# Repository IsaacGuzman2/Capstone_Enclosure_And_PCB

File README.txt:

Hi future student!

IF you are reading this congrats you get to continue a cool project that I had the pleasure of getting to start for my capstone.

This folder contains the enclosures and PCB files that I made for this project. I was mainly in charge of the more physical aspects of this project so any questions about that you can contact me about through my school email (guzmange@oregonstate.edu) 

I'd be more then happy to help with any questions. This stuff is free use so don't be afraid to delete, add, or modify in any way you see fit. I understand you will have to make your own engineering requirements so go off I guess. 

I wish you the best in this project don't forget to communicate with Gerrad he has some good ideas and even is really motivating. This project has some real impact so be proud of what you accomplish and relly try your best and you will be rewarded by making a positive impact in the world. 

Godspeed homies

Gerardo Isaac Guzman

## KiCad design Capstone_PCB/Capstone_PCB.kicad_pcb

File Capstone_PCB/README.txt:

Hi again future student!

This here is the Kicad Project files for the Main PCB 

This PCB has the schematic and pcb files for the project as well as a folder for the gerber files to get our final version of the PCB printed by OSHPark

There should also be a .csv file here with the BOM that should help find which parts are needed in case something happens with carrying over the files. 

I HIGHLY reccomend ordering at another PCB print shop other then OSHPark because of the cost. It is a 2-layer board but it costs about $45+ with no rushed shipping (12-15 days) so it can get expensive. Please look at other options when ordering if money is an issue. 

Hopefully this file helps as always fell free to make adjustments to meet the capstone class requirements. 

Godspeed homies,

Gerardo Isaac Guzman

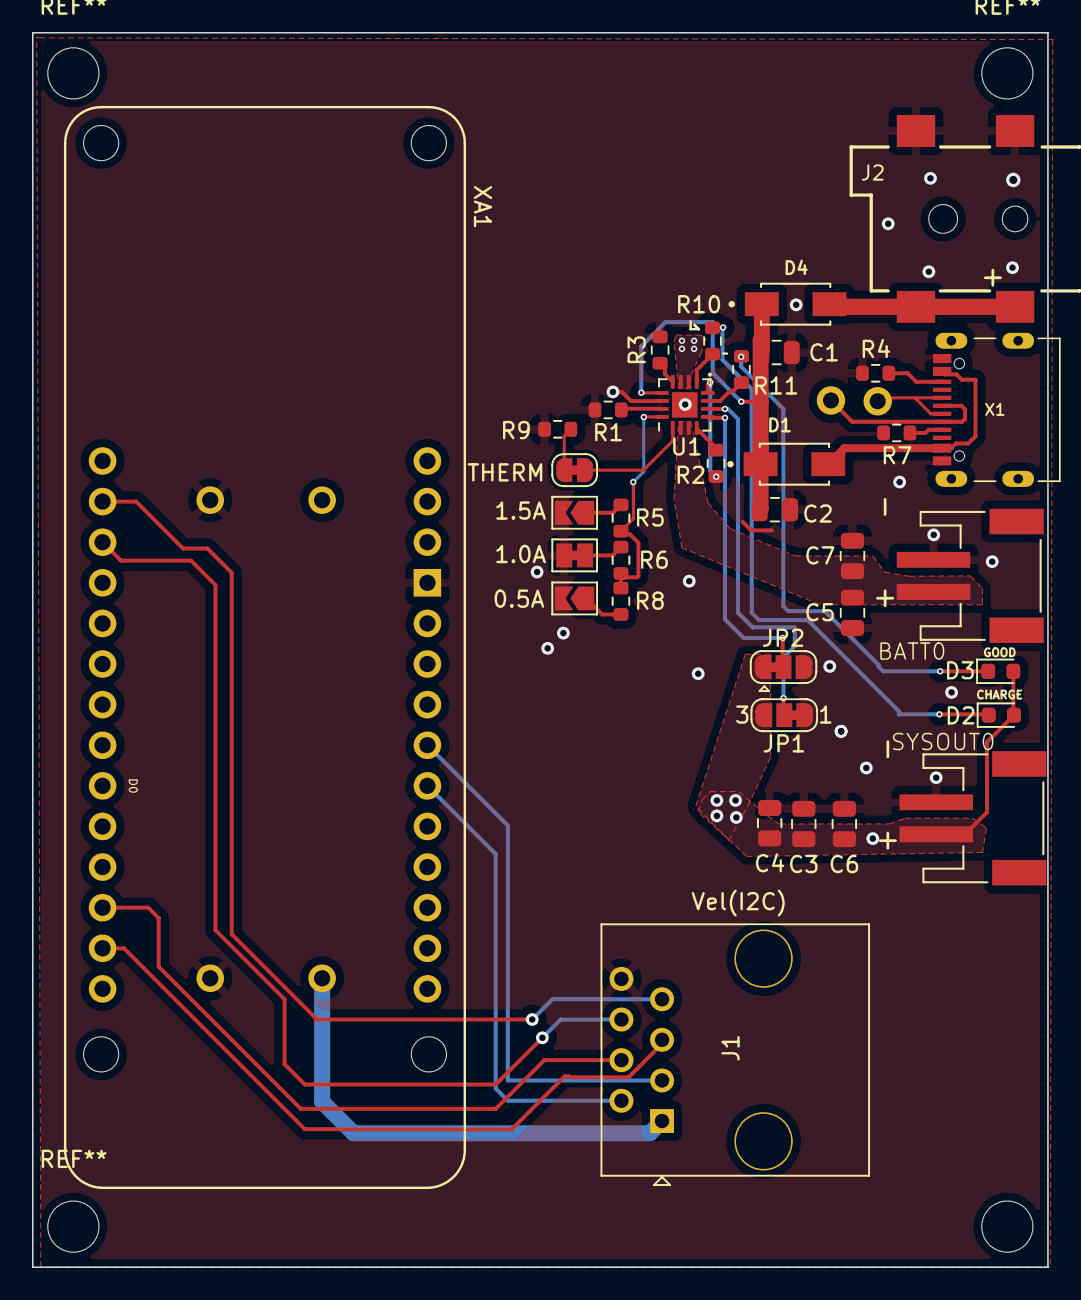
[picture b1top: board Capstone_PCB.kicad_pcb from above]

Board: 2 copper layers, 63.5 x 77.2 mm, 35 parts (0 on the bottom side), 31 nets.

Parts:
BATT0: JST 2PH; JST-PH-2-SMT-RA
C1, C2: 10uF; C_0805_2012Metric
C3, C4, C5, C6, C7: 10UF; C_0805_2012Metric
D1, D4: SK34A; DIOM4325X250N
D2, D3: LED; LED_0603_1608Metric
J1: RJ45; RJ45_OST_PJ012-8P8CX_Vertical
J2: 2.1mm DC; DCJACK_2MM_SMT
JP1: SolderJumper_3_Bridged12; SolderJumper-3_P1.3mm_Bridged12_RoundedPad1.0x1.5mm_NumberL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
JP2: SolderJumper_3_Bridged12; SolderJumper-3_P1.3mm_Bridged12_RoundedPad1.0x1.5mm
JP3: 1.5A; SolderJumper-2_P1.3mm_Open_TrianglePad1.0x1.5mm
JP4: 1.0A; SolderJumper-2_P1.3mm_Bridged_Pad1.0x1.5mm
JP5: 0.5A; SolderJumper-2_P1.3mm_Open_TrianglePad1.0x1.5mm
JP6: THERM; SolderJumper-2_P1.3mm_Bridged_RoundedPad1.0x1.5mm
R1, R2, R9, R10, R11: 10K; R_0603_1608Metric
R3, R6: 1K; R_0603_1608Metric
R4, R7: 5.1K; R_0603_1608Metric
R5: 590; R_0603_1608Metric
R8: 2K; R_0603_1608Metric
SYSOUT0: JST 2PH; JST-PH-2-SMT-RA
U1: BQ24074RGT; VQFN-16-1EP_3x3mm_P0.5mm_EP1.6x1.6mm
X1: USB Type C; USB_C_CUSB31-CFM2AX-01-X
XA1: Arduino_MKR_NB_1500_Socket; Arduino_MKR_FOX_1200_Socket

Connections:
/A0: J1.7, XA1.A0 (A0/DAC)
/A1: J1.6, XA1.A1
/CC1: R7.1, X1.A5
/CC2: R4.1, X1.B5
/CE: R2.1, U1.4 (~CE)
/CHARGE: R10.2, U1.9 (~CHG)
/D3: J1.4, XA1.D3
/D4: J1.5, XA1.D4
/D+: X1.A6, X1.B6
/D-: X1.A7, X1.B7
/EN1: JP1.2 (C), U1.6 (EN1)
/EN2: JP2.2 (C), U1.5 (EN2)
/GOOD: R11.1, U1.7 (~PGOOD)
/ILIM: R3.1, U1.12 (ILIM)
/ISET: R5.1, R6.1, R8.1, U1.16 (ISET)
/ITERM: R1.1, U1.15 (ITERM)
/LIPO: BATT0.1, C5.1, C7.1, U1.2 (BAT), U1.3 (BAT)
/OUT: C3.1, C4.1, C6.1, D2.2 (A), D3.2 (A), J1.1, JP1.3 (B), JP2.1 (A), SYSOUT0.1, U1.10 (OUT), U1.11 (OUT), XA1.VIN
/SCL: J1.3, XA1.D12 (D12_SCL)
/SDA: J1.2, XA1.D11 (D11_SDA)
/TS: JP6.2 (B), U1.1 (TS)
/VIN: C1.1, C2.1, D1.C, D4.C, U1.13 (IN)
/VUSB: D1.A, X1.A4B9, X1.B4A9
GND: BATT0.2, C1.2, C2.2, C3.2, C4.2, C5.2, C6.2, C7.2, J1.8, J2.2, J2.3, JP1.1 (A), JP2.3 (B), JP3.2 (B), JP4.2 (B), JP5.2 (B), R1.2, R2.2, R3.2, R4.2, R7.2, R9.2, SYSOUT0.2, U1.8 (VSS), U1.14 (TMR), U1.17 (VSS), X1.A1B12, X1.B1A12, XA1.GND
unnamed: D2.1 (K), R10.1
unnamed: D3.1 (K), R11.2
unnamed: D4.A, J2.1, J2.1'
unnamed: JP3.1 (A), R5.2
unnamed: JP4.1 (A), R6.2
unnamed: JP5.1 (A), R8.2
unnamed: JP6.1 (A), R9.1
